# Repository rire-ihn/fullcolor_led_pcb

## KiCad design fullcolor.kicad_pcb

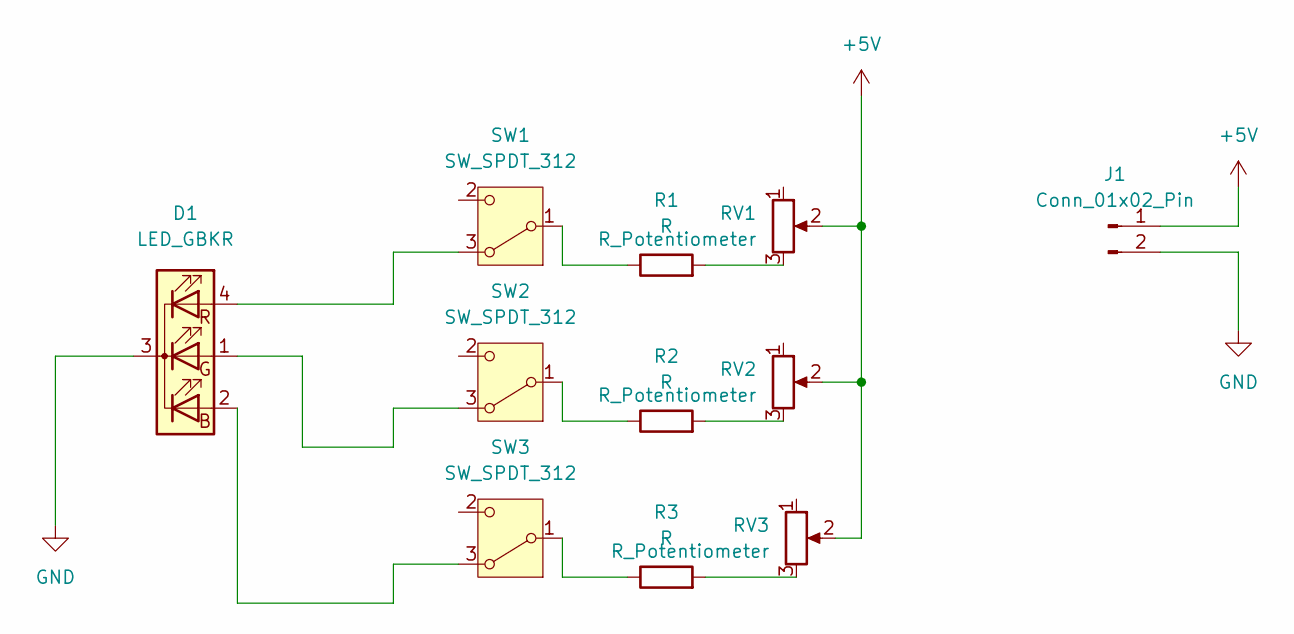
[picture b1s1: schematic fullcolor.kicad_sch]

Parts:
D1: LED_GBKR; LED_D5.0mm-4_RGB_Wide_Pins
J1: Conn_01x02_Pin; JST_XH_S2B-XH-A-1_1x02_P2.50mm_Horizontal
R1, R2, R3: R; R_Axial_DIN0207_L6.3mm_D2.5mm_P10.16mm_Horizontal
RV1, RV2, RV3: R_Potentiometer; potention_3386k
SW1, SW2, SW3: SW_SPDT_312; SW_Slide-03_Wuerth-WS-SLTV_10x2.5x6.4_P2.54mm

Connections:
+5V: J1.1, RV1.2, RV2.2, RV3.2
GND: D1.3 (K), J1.2
unnamed: D1.2 (BA), SW3.3 (A)
unnamed: D1.1 (GA), SW2.3 (A)
unnamed: D1.4 (RA), SW1.3 (A)
unnamed: R1.2, RV1.3
unnamed: R2.2, RV2.3
unnamed: R3.2, RV3.3
unnamed: R1.1, SW1.1 (B)
unnamed: R2.1, SW2.1 (B)
unnamed: R3.1, SW3.1 (B)

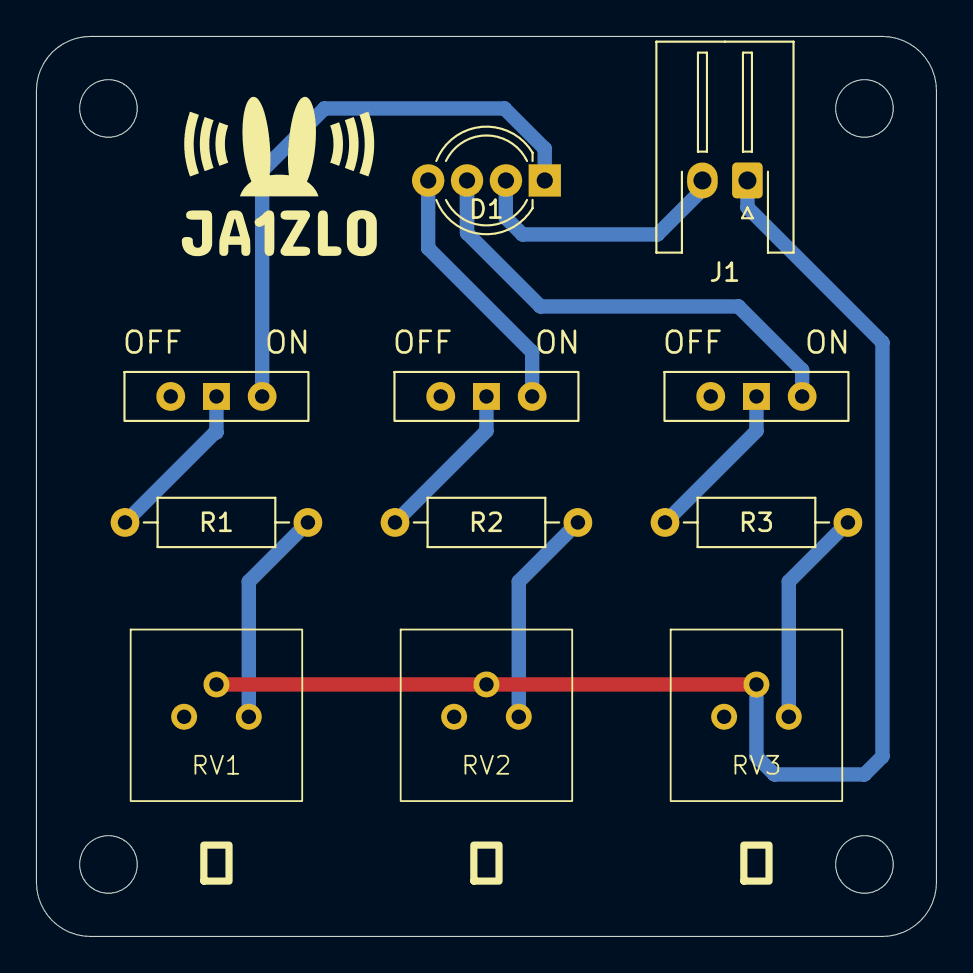
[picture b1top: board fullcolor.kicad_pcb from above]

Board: 2 copper layers, 50.0 x 50.0 mm, 11 parts (0 on the bottom side), 11 nets.

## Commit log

2024-11-18 initial
